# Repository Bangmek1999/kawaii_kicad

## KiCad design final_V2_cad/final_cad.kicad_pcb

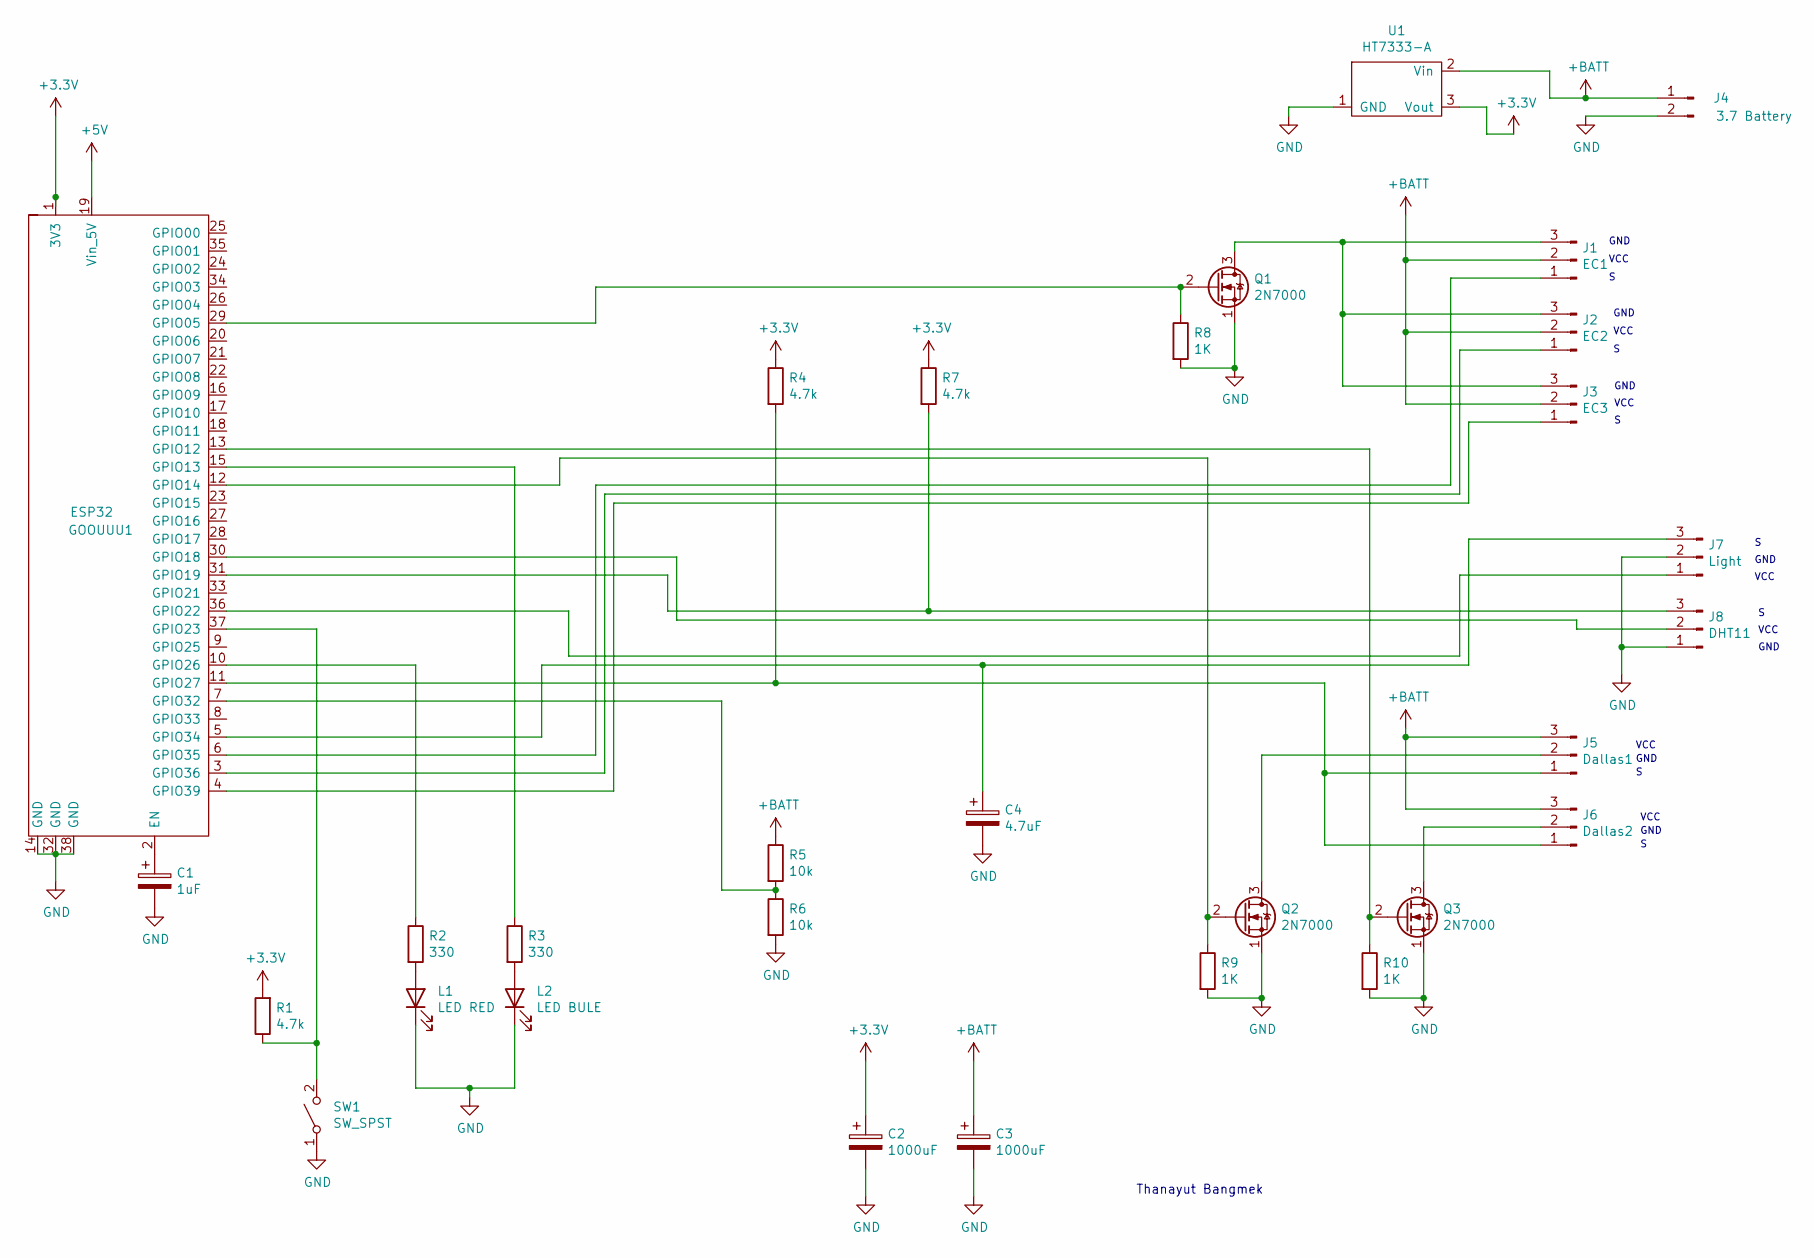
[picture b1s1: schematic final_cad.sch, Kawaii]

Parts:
C1: 1uF; CP_Radial_D5.0mm_P2.50mm
C2, C3: 1000uF; CP_Radial_D8.0mm_P2.50mm
C4: 4.7uF; CP_Radial_D5.0mm_P2.50mm
GOOUUU1: ESP32; esp32
J1: EC1; JST_EH_B3B-EH-A_1x03_P2.50mm_Vertical
J2: EC2; JST_EH_B3B-EH-A_1x03_P2.50mm_Vertical
J3: EC3; JST_EH_B3B-EH-A_1x03_P2.50mm_Vertical
J4: 3.7 Battery; JST_EH_B2B-EH-A_1x02_P2.50mm_Vertical
J5: Dallas1; JST_EH_B3B-EH-A_1x03_P2.50mm_Vertical
J6: Dallas2; JST_EH_B3B-EH-A_1x03_P2.50mm_Vertical
J7: Light; JST_EH_B3B-EH-A_1x03_P2.50mm_Vertical
J8: DHT11; JST_EH_B3B-EH-A_1x03_P2.50mm_Vertical
L1: LED RED; LED_D5.0mm
L2: LED BULE; LED_D5.0mm
Q1, Q2, Q3: 2N7000; TO-92_Inline
R1, R4, R7: 4.7k; R_Axial_DIN0207_L6.3mm_D2.5mm_P10.16mm_Horizontal
R2, R3: 330; R_Axial_DIN0207_L6.3mm_D2.5mm_P10.16mm_Horizontal
R5, R6: 10k; R_Axial_DIN0207_L6.3mm_D2.5mm_P10.16mm_Horizontal
R8, R9, R10: 1K; R_Axial_DIN0207_L6.3mm_D2.5mm_P10.16mm_Horizontal
SW1: SW_SPST; SW_PUSH_6mm
U1: HT7333-A; TO-92_Inline

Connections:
+3V3: C2.1, GOOUUU1.1 (3V3), R1.2, R4.1, R7.1, U1.3 (Vout)
+5V: GOOUUU1.19 (Vin_5V)
+BATT: C3.1, J1.2, J2.2, J3.2, J4.1, J5.3, J6.3, R5.1, U1.2 (Vin)
GND: C1.2, C2.2, C3.2, C4.2, GOOUUU1.14 (GND), GOOUUU1.32 (GND), GOOUUU1.38 (GND), J4.2, J7.2, J8.1, L1.1 (K), L2.1 (K), Q1.1 (S), Q2.1 (S), Q3.1 (S), R6.2, R8.2, R9.2, R10.2, SW1.1 (A), U1.1 (GND)
unnamed: C1.1, GOOUUU1.2 (EN)
unnamed: C4.1, GOOUUU1.5 (GPIO34), J7.3
unnamed: GOOUUU1.3 (GPIO36), J2.1
unnamed: GOOUUU1.4 (GPIO39), J3.1
unnamed: GOOUUU1.6 (GPIO35), J1.1
unnamed: GOOUUU1.7 (GPIO32), R5.2, R6.1
unnamed: GOOUUU1.10 (GPIO26), R2.1
unnamed: GOOUUU1.11 (GPIO27), J5.1, J6.1, R4.2
unnamed: GOOUUU1.12 (GPIO14), Q2.2 (G), R9.1
unnamed: GOOUUU1.13 (GPIO12), Q3.2 (G), R10.1
unnamed: GOOUUU1.15 (GPIO13), R3.1
unnamed: GOOUUU1.29 (GPIO05), Q1.2 (G), R8.1
unnamed: GOOUUU1.30 (GPIO18), J8.2
unnamed: GOOUUU1.31 (GPIO19), J8.3, R7.2
unnamed: GOOUUU1.36 (GPIO22), J7.1
unnamed: GOOUUU1.37 (GPIO23), R1.1, SW1.2 (B)
unnamed: J1.3, J2.3, J3.3, Q1.3 (D)
unnamed: J5.2, Q2.3 (D)
unnamed: J6.2, Q3.3 (D)
unnamed: L1.2 (A), R2.2
unnamed: L2.2 (A), R3.2

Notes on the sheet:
Thanayut Bangmek
GND
VCC

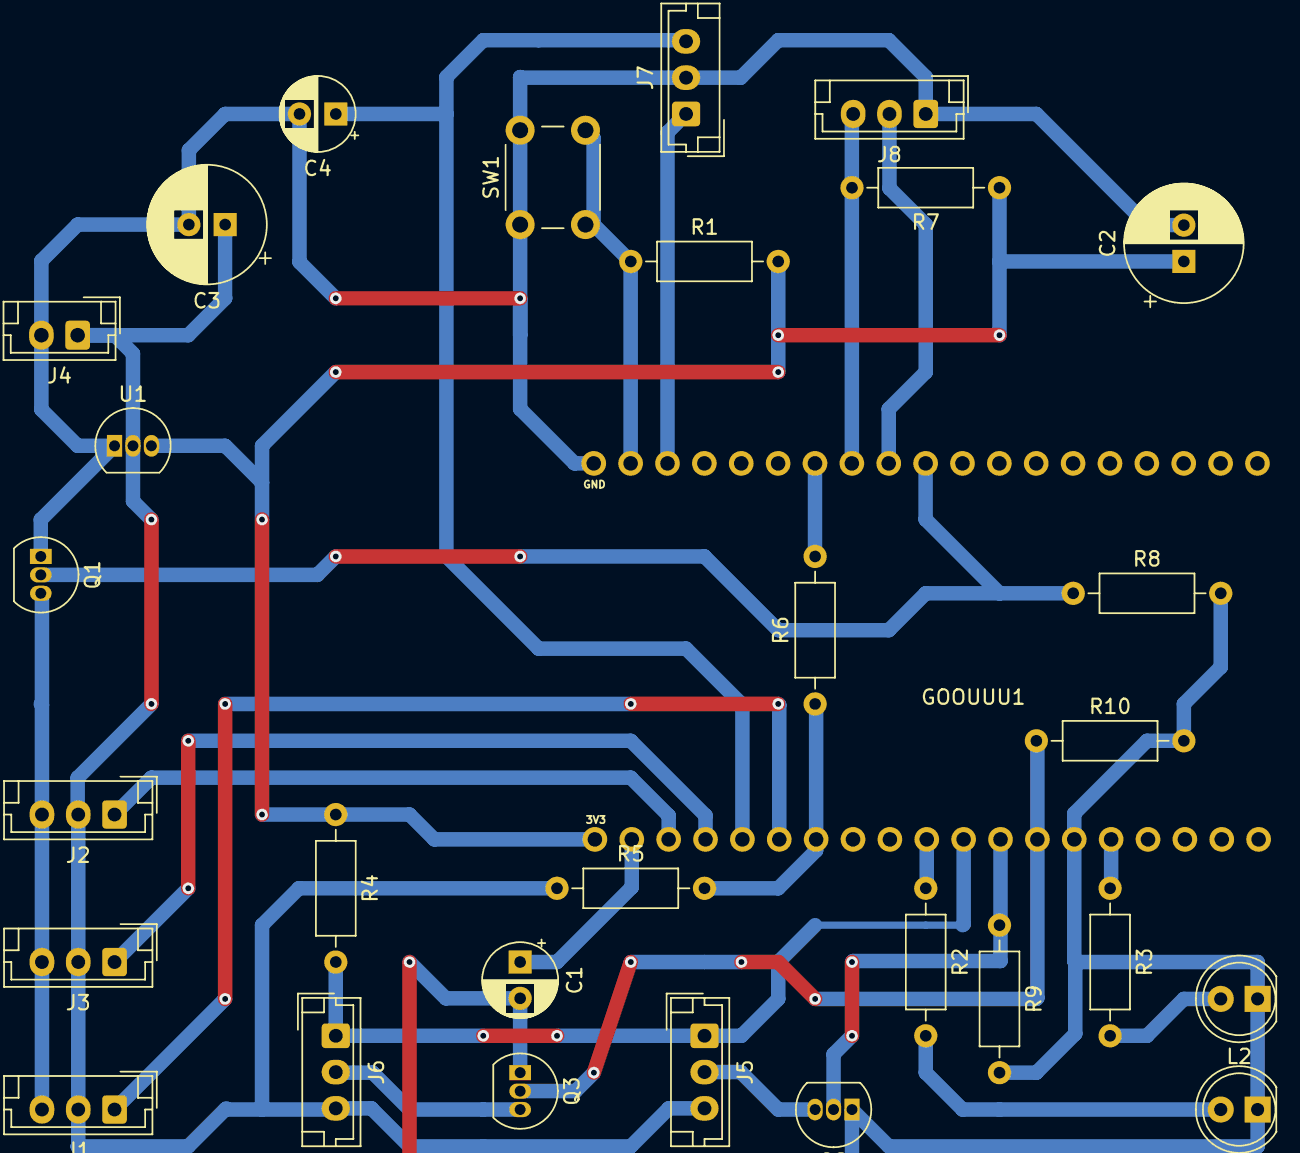
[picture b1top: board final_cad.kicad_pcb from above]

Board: 2 copper layers, 30 parts (0 on the bottom side), 24 nets.

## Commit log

2021-07-25 project commit
